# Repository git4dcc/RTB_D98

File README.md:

# RTB_D98

## This is a [opendcc](https://forum.opendcc.de/viewtopic.php?t=11034) forum project
The hard and software is based on the [D16](https://rtb4dcc.de/hardware/decoder/d16/) motor decoder. It implements a double-sided NEM-651 **function decoder** for use with DCC infrastructure. The hardware provides
- 10 auxiliary output ports
- up to 32 WS281x neo pixels

``Note: this repo is currently under construction and will be completed soon. (Feb 20, 2026)``

<details>
<summary>See also</summary>

- [RTB_D16 - NEM651](/../../../../git4dcc/RTB_D16)

</details>

<details>
<summary>User Guides</summary>

- User Guide - DE
- User Guide - EN

</details>

<br>

The decoder has the following features,
- **NEM-651** connector
- **DCC**
  - DCC-A automatic logon
  - DCC-R protocol extension
  - Service Mode Programming
- **Railcom**
  - Channel 1/2
  - POM, xPOM, Long_1
  - DYN: QoS, Track-voltage, AUX-current, Temp, East/West
- double sided
- Dimension: 13 x 9 mm
- 5-20V track voltage
- heartbeat LED
- adjustable max AUX current (default 500mA)
- over temp protection
- **Function output**
  - LV/LR/AUX1/AUX2 open drain
  - AUX3/AUX4/AUX5/AUX6/AUX7/AUX8 logic level (5V)
  - LV/LR/AUX1/AUX2/AUX3/AUX4 (dimmable, 1.4kHz)
  - WS281x: up to 32 WS28xx neo pixels
- optional external buffer capacitor (max. 1500uF)
- <10mA idle power consumption
- Firmware update over main tracks via DCC-R protocol

# Hardware
The current PCB layout uses SMD footprints with 0.5mm pitch and mainly 0402 parts. Reflow soldering is recommended, handsoldering nearly impossible.

## PCB
- 6-layer PCB, FR4, 13 x 9 x 0.8mm (double sided)
- CPU: AVR64DA32
- Connector: NEM-651 (or solder)

## Kicad
[Schematic](doc/D98_schematic.pdf) | [Layout](doc/D98_layout.pdf) | [Gerber](gerber)

<details>
<summary>Dependency</summary>
<br>

:yellow_circle: Requires my Kicad project library [RTB_SamacSys](https://github.com/git4dcc/RTB_SamacSys) in the same directory tree.

</details>

## Firmware
Filename structure: { **pcb** }{ **code** }{ **version** }.hex

Example: **D98F0001**.hex

|   | Description |
| --- | --- |
| **pcb** | Name of matching hardware (**D98**) |
| **code** | Type of code contained (**R**=rom, **B**=bootloader, **F**=flash, **U**=bld update, **P**=UPDI factory code) |
| **version** | Release version (**####**) |

[Firmware files](firmware)

# Images
| top | bottom |
| --- | --- |
|  |  |

# YouTube
Some YouTubes to see the D98 decoder in action.<br><br>

This project is intended for hobby use only and is distributed in accordance with the Apache License 2.0 agreement.

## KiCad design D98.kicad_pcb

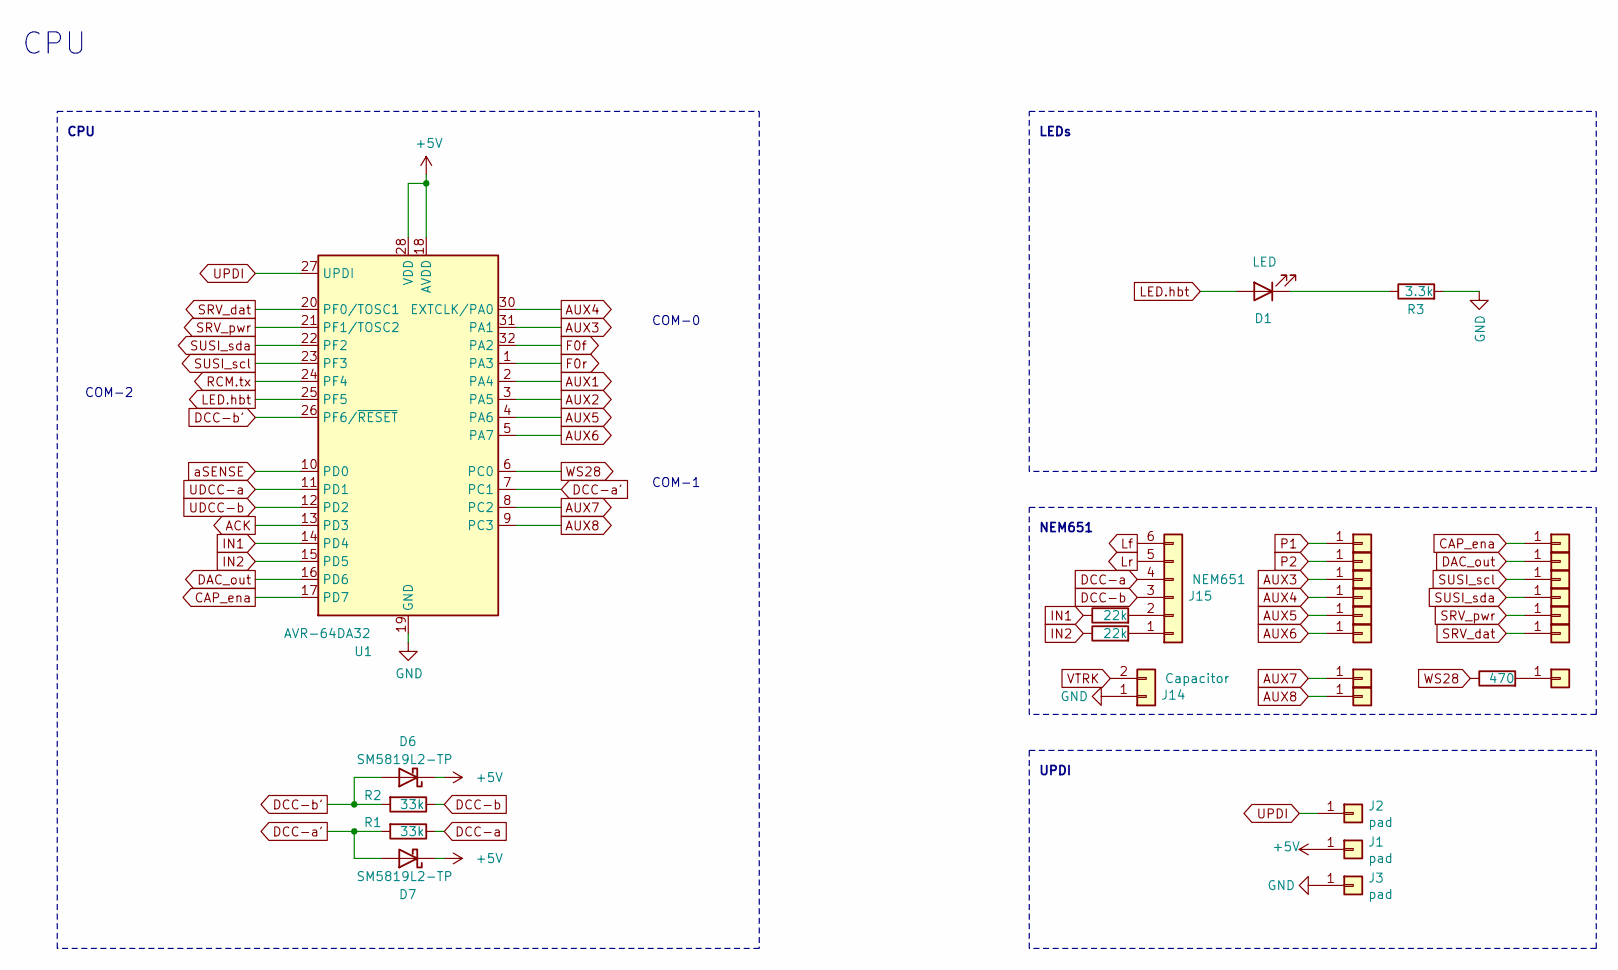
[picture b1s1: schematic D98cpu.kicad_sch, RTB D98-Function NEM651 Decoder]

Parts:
D1: LED; LED_0402_1005Metric
D6, D7: SM5819L2-TP; SM5819L2TP
J1, J2, J3, J6, J7, J8, J9, J10, J11, J12, J13, J16, J17, J18, J19, J20, J21, J22: pad; Solder_Pad_1x1mm
J14: Capacitor; PinHeader_1x02_P1.27mm_Horizontal
J15: NEM651; PinHeader_1x06_P1.27mm_Horizontal
R1, R2: 33k; R_0402_1005Metric
R3: 3.3k; R_0402_1005Metric
R13, R14: 22k; R_0402_1005Metric
R16: 470; R_0402_1005Metric
U1: AVR-64DA32; VQFN-32-1EP_5x5mm_P0.5mm_EP3.1x3.1mm

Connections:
+5V: D6.1 (K), D7.1 (K), J1.1, U1.18 (AVDD), U1.28 (VDD); also elsewhere on the board
ACK: U1.13 (PD3); also elsewhere on the board
AUX1: U1.2 (PA4); also elsewhere on the board
AUX2: U1.3 (PA5); also elsewhere on the board
AUX3: J17.1, U1.31 (PA1)
AUX4: J12.1, U1.30 (EXTCLK/PA0)
AUX5: J19.1, U1.4 (PA6)
AUX6: J11.1, U1.5 (PA7)
AUX7: J20.1, U1.8 (PC2)
AUX8: J21.1, U1.9 (PC3)
CAP_ena: J13.1, U1.17 (PD7)
DAC_out: J7.1, U1.16 (PD6)
DCC-a: J15.4, R1.1; also elsewhere on the board
DCC-a': D7.2 (A), R1.2, U1.7 (PC1)
DCC-b: J15.3, R2.1; also elsewhere on the board
DCC-b': D6.2 (A), R2.2, U1.26 (PF6/~RESET)
F0f: U1.32 (PA2); also elsewhere on the board
F0r: U1.1 (PA3); also elsewhere on the board
GND: J3.1, J14.1, R3.2, U1.19 (GND), U1.29 (GND), U1.33 (GND); also elsewhere on the board
IN1: R13.1, U1.14 (PD4)
IN2: R14.1, U1.15 (PD5)
LED.hbt: D1.2 (A), U1.25 (PF5)
Lf: J15.6; also elsewhere on the board
Lr: J15.5; also elsewhere on the board
unnamed: D1.1 (K), R3.1
unnamed: J15.1, R14.2
unnamed: J15.2, R13.2
unnamed: J22.1, R16.2
P1: J8.1; also elsewhere on the board
P2: J9.1; also elsewhere on the board
RCM.tx: U1.24 (PF4); also elsewhere on the board
SRV_dat: J18.1, U1.20 (PF0/TOSC1)
SRV_pwr: J16.1, U1.21 (PF1/TOSC2)
SUSI_scl: J6.1, U1.23 (PF3)
SUSI_sda: J10.1, U1.22 (PF2)
UDCC-a: U1.11 (PD1); also elsewhere on the board
UDCC-b: U1.12 (PD2); also elsewhere on the board
UPDI: J2.1, U1.27 (UPDI)
VTRK: J14.2; also elsewhere on the board
WS28: R16.1, U1.6 (PC0)
aSENSE: U1.10 (PD0); also elsewhere on the board

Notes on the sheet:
UPDI
COM-2
COM-0
CPU
NEM651
LEDs
COM-1

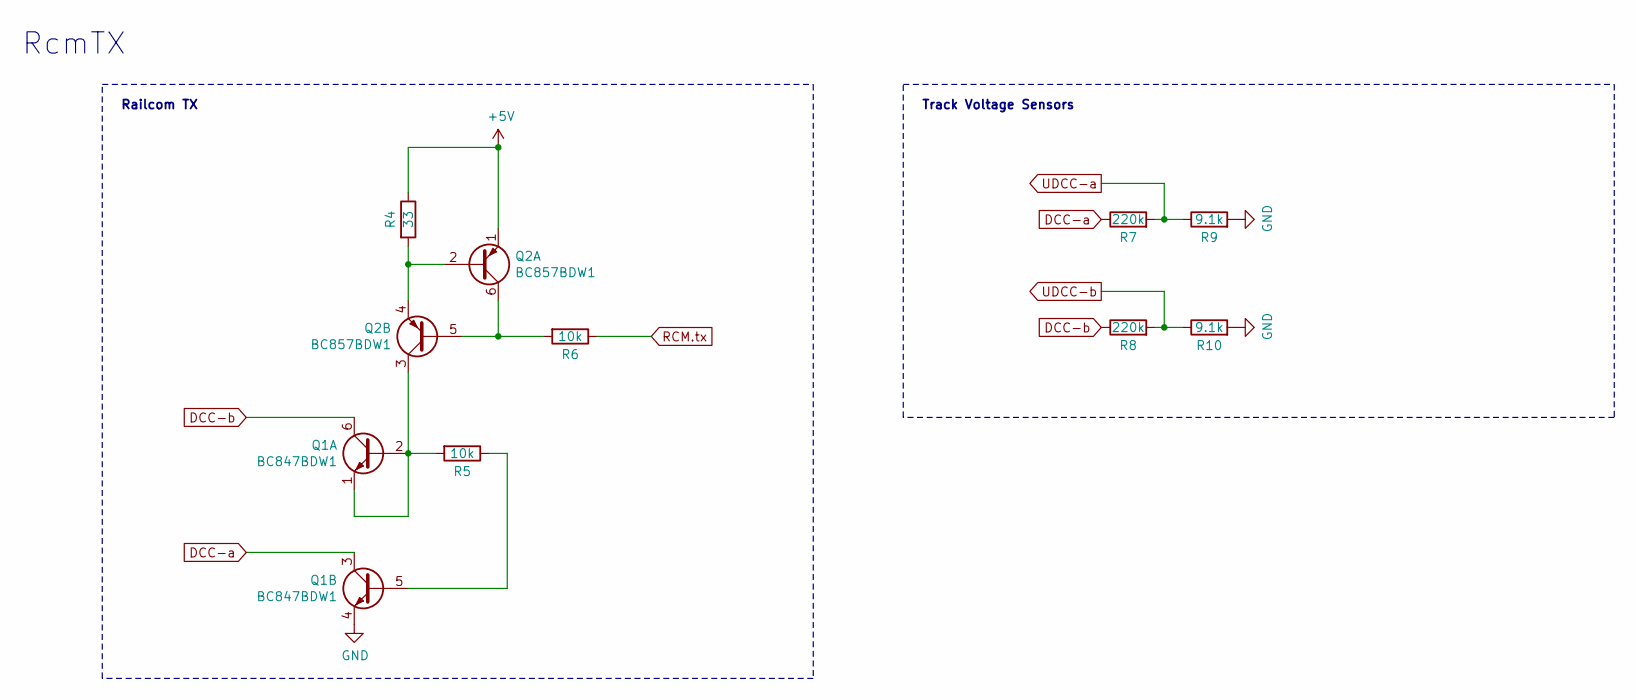
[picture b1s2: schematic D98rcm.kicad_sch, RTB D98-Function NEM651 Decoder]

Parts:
Q1: BC847BDW1; SOT-666
Q2: BC857BDW1; SOT-666
R4: 33; R_0402_1005Metric
R5, R6: 10k; R_0402_1005Metric
R7, R8: 220k; R_0402_1005Metric
R9, R10: 9.1k; R_0402_1005Metric

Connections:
+5V: Q2.1 (E1), R4.1; also elsewhere on the board
DCC-a: Q1.3 (C2), R7.1; also elsewhere on the board
DCC-b: Q1.6 (C1), R8.1; also elsewhere on the board
GND: Q1.4 (E2), R9.2, R10.2; also elsewhere on the board
unnamed: Q1.1 (E1), Q1.2 (B1), Q2.3 (C2), R5.2
unnamed: Q1.5 (B2), R5.1
unnamed: Q2.2 (B1), Q2.4 (E2), R4.2
unnamed: Q2.5 (B2), Q2.6 (C1), R6.2
RCM.tx: R6.1; also elsewhere on the board
UDCC-a: R7.2, R9.1; also elsewhere on the board
UDCC-b: R8.2, R10.1; also elsewhere on the board

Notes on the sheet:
Railcom TX
Track Voltage Sensors
RcmTX

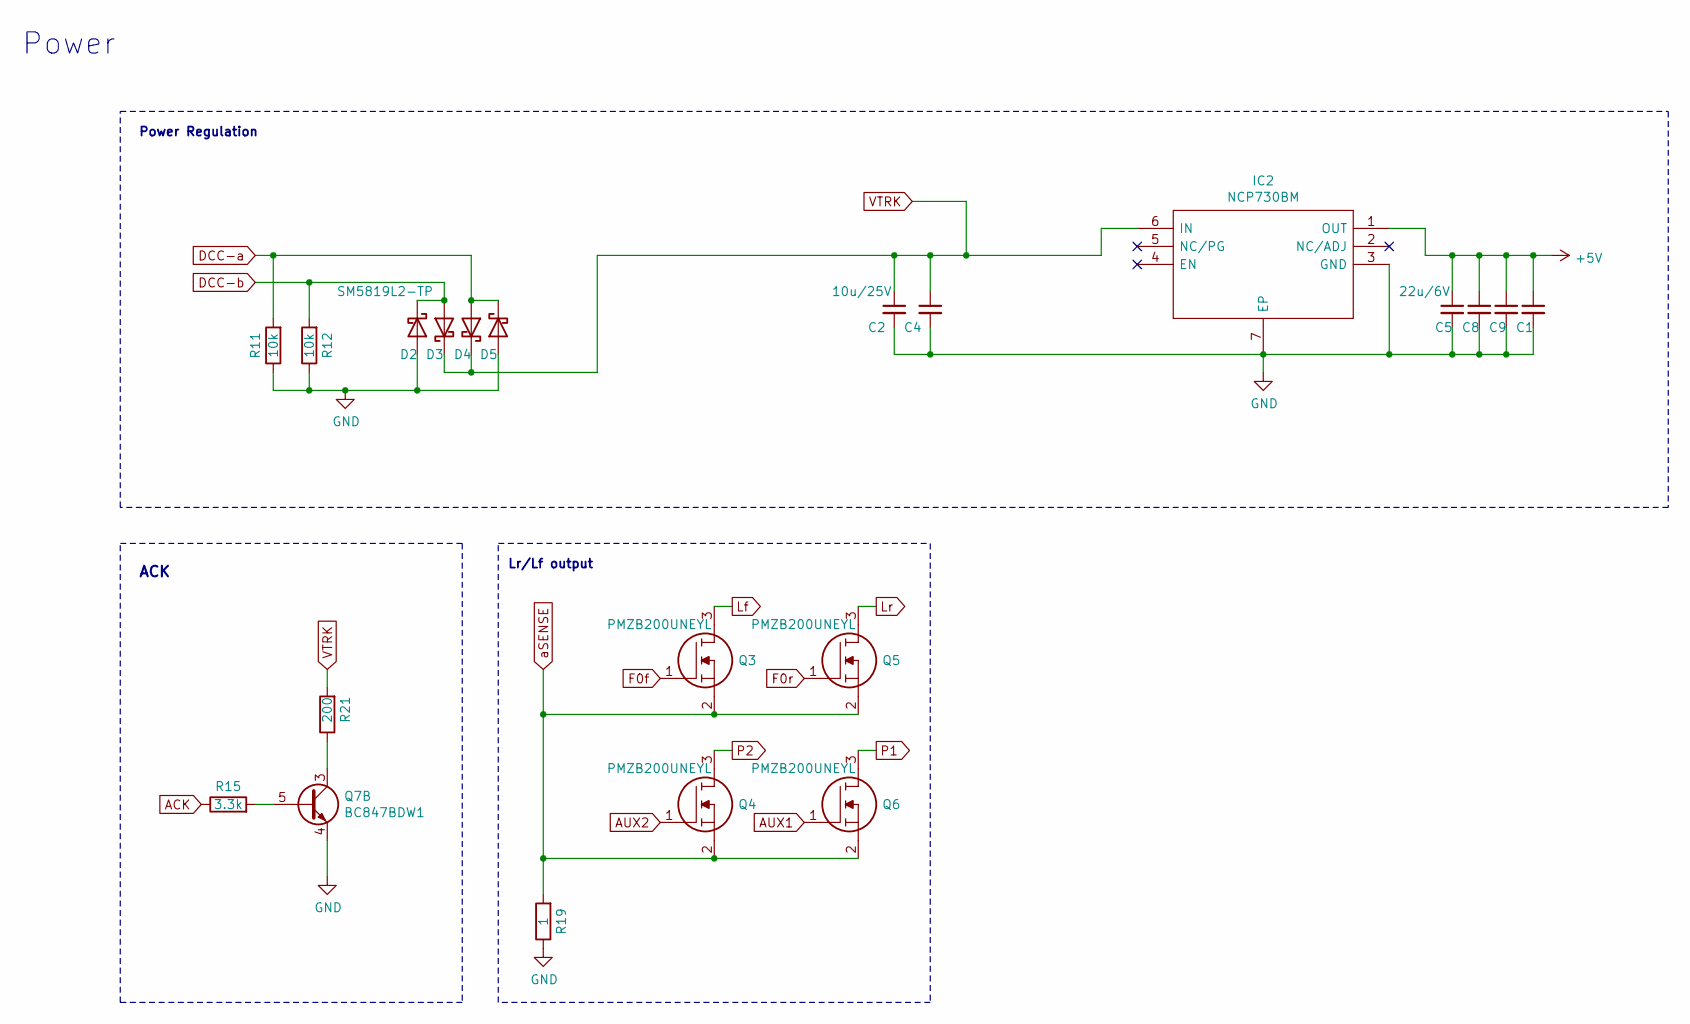
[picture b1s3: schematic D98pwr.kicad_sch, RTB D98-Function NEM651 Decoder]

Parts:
C1, C5, C8, C9: 22u/6V; C_0402_1005Metric
C2, C4: 10u/25V; C_0603_1608Metric
D2, D3, D4, D5: SM5819L2-TP; SM5819L2TP
IC2: NCP730BM; WSON-6-1EP_2x2mm_P0.65mm_EP1x1.6mm_ThermalVias; Mouser Part Number 863-NCP730BMT330TBG
Q3, Q4, Q5, Q6: PMZB200UNEYL; Diodes_DFN1006-3; Mouser Part Number 771-PMZB200UNEYL
Q7: BC847BDW1; SOT-666
R11, R12: 10k; R_0402_1005Metric
R15: 3.3k; R_0402_1005Metric; JLCPCB C25890
R19: 1; R_0402_1005Metric
R21: 200; R_0603_1608Metric; JLCPCB C8218

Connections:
+5V: C1.1, C5.1, C8.1, C9.1, IC2.1 (OUT); also elsewhere on the board
ACK: R15.1; also elsewhere on the board
AUX1: Q6.1; also elsewhere on the board
AUX2: Q4.1; also elsewhere on the board
DCC-a: D4.2 (A), D5.1 (K), R11.2; also elsewhere on the board
DCC-b: D2.1 (K), D3.2 (A), R12.2; also elsewhere on the board
F0f: Q3.1; also elsewhere on the board
F0r: Q5.1; also elsewhere on the board
GND: C1.2, C2.2, C4.2, C5.2, C8.2, C9.2, D2.2 (A), D5.2 (A), IC2.3 (GND), IC2.7 (EP), Q7.4 (E2), R11.1, R12.1, R19.1; also elsewhere on the board
Lf: Q3.3; also elsewhere on the board
Lr: Q5.3; also elsewhere on the board
unnamed: Q7.5 (B2), R15.2
unnamed: Q7.3 (C2), R21.1
P1: Q6.3; also elsewhere on the board
P2: Q4.3; also elsewhere on the board
VTRK: C2.1, C4.1, D3.1 (K), D4.1 (K), IC2.6 (IN), R21.2; also elsewhere on the board
aSENSE: Q3.2, Q4.2, Q5.2, Q6.2, R19.2; also elsewhere on the board

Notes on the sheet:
ACK
Lr/Lf output
Power
Power Regulation

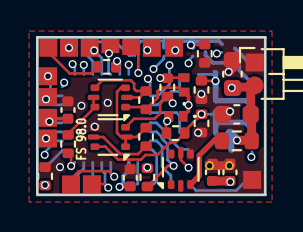
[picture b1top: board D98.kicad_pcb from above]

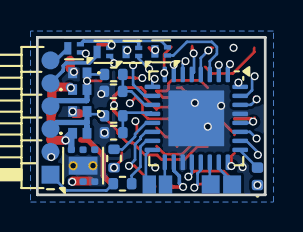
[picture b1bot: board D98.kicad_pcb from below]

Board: 4 copper layers, 12.7 x 8.8 mm, 60 parts (22 on the bottom side), 47 nets.

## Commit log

2026-02-20 initial
2026-02-20 Change image width in README
    Updated image size in README from 800 to 500 pixels.
2026-02-20 Revise README with project details and features
    Updated project description and added details about hardware features.
2026-02-20 Add construction notice to README
    Added a note indicating that the repository is under construction and will be completed soon.
2026-02-20 git mirror test
2026-02-20 Revise README for Railcom and WS28xx details
    Updated features and specifications for clarity.
2026-02-20 Revise function output details in README
    Updated function output specifications for clarity and corrected AUX3-AUX8 logic level voltage.
2026-02-22 Fix badge title and update project description
    Updated badge and project description in README.

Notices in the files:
D98.kicad_pcb:
Licensed under the Apache License, Version 2
